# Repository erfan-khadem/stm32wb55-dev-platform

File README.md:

# stm32wb55-dev-platform
An Evaluation and Development Platform For STM32WB55CGU6 MicroController with a few Sensors.

Note that the PCB is designed in 4 layers.

[Schematics pdf](https://github.com/erfan-khadem/stm32wb55-dev-platform/blob/main/stm32wb55-dev.pdf)

[Assembled PCB Picture](https://github.com/erfan-khadem/stm32wb55-dev-platform/blob/main/assembled.jpg?raw=true)

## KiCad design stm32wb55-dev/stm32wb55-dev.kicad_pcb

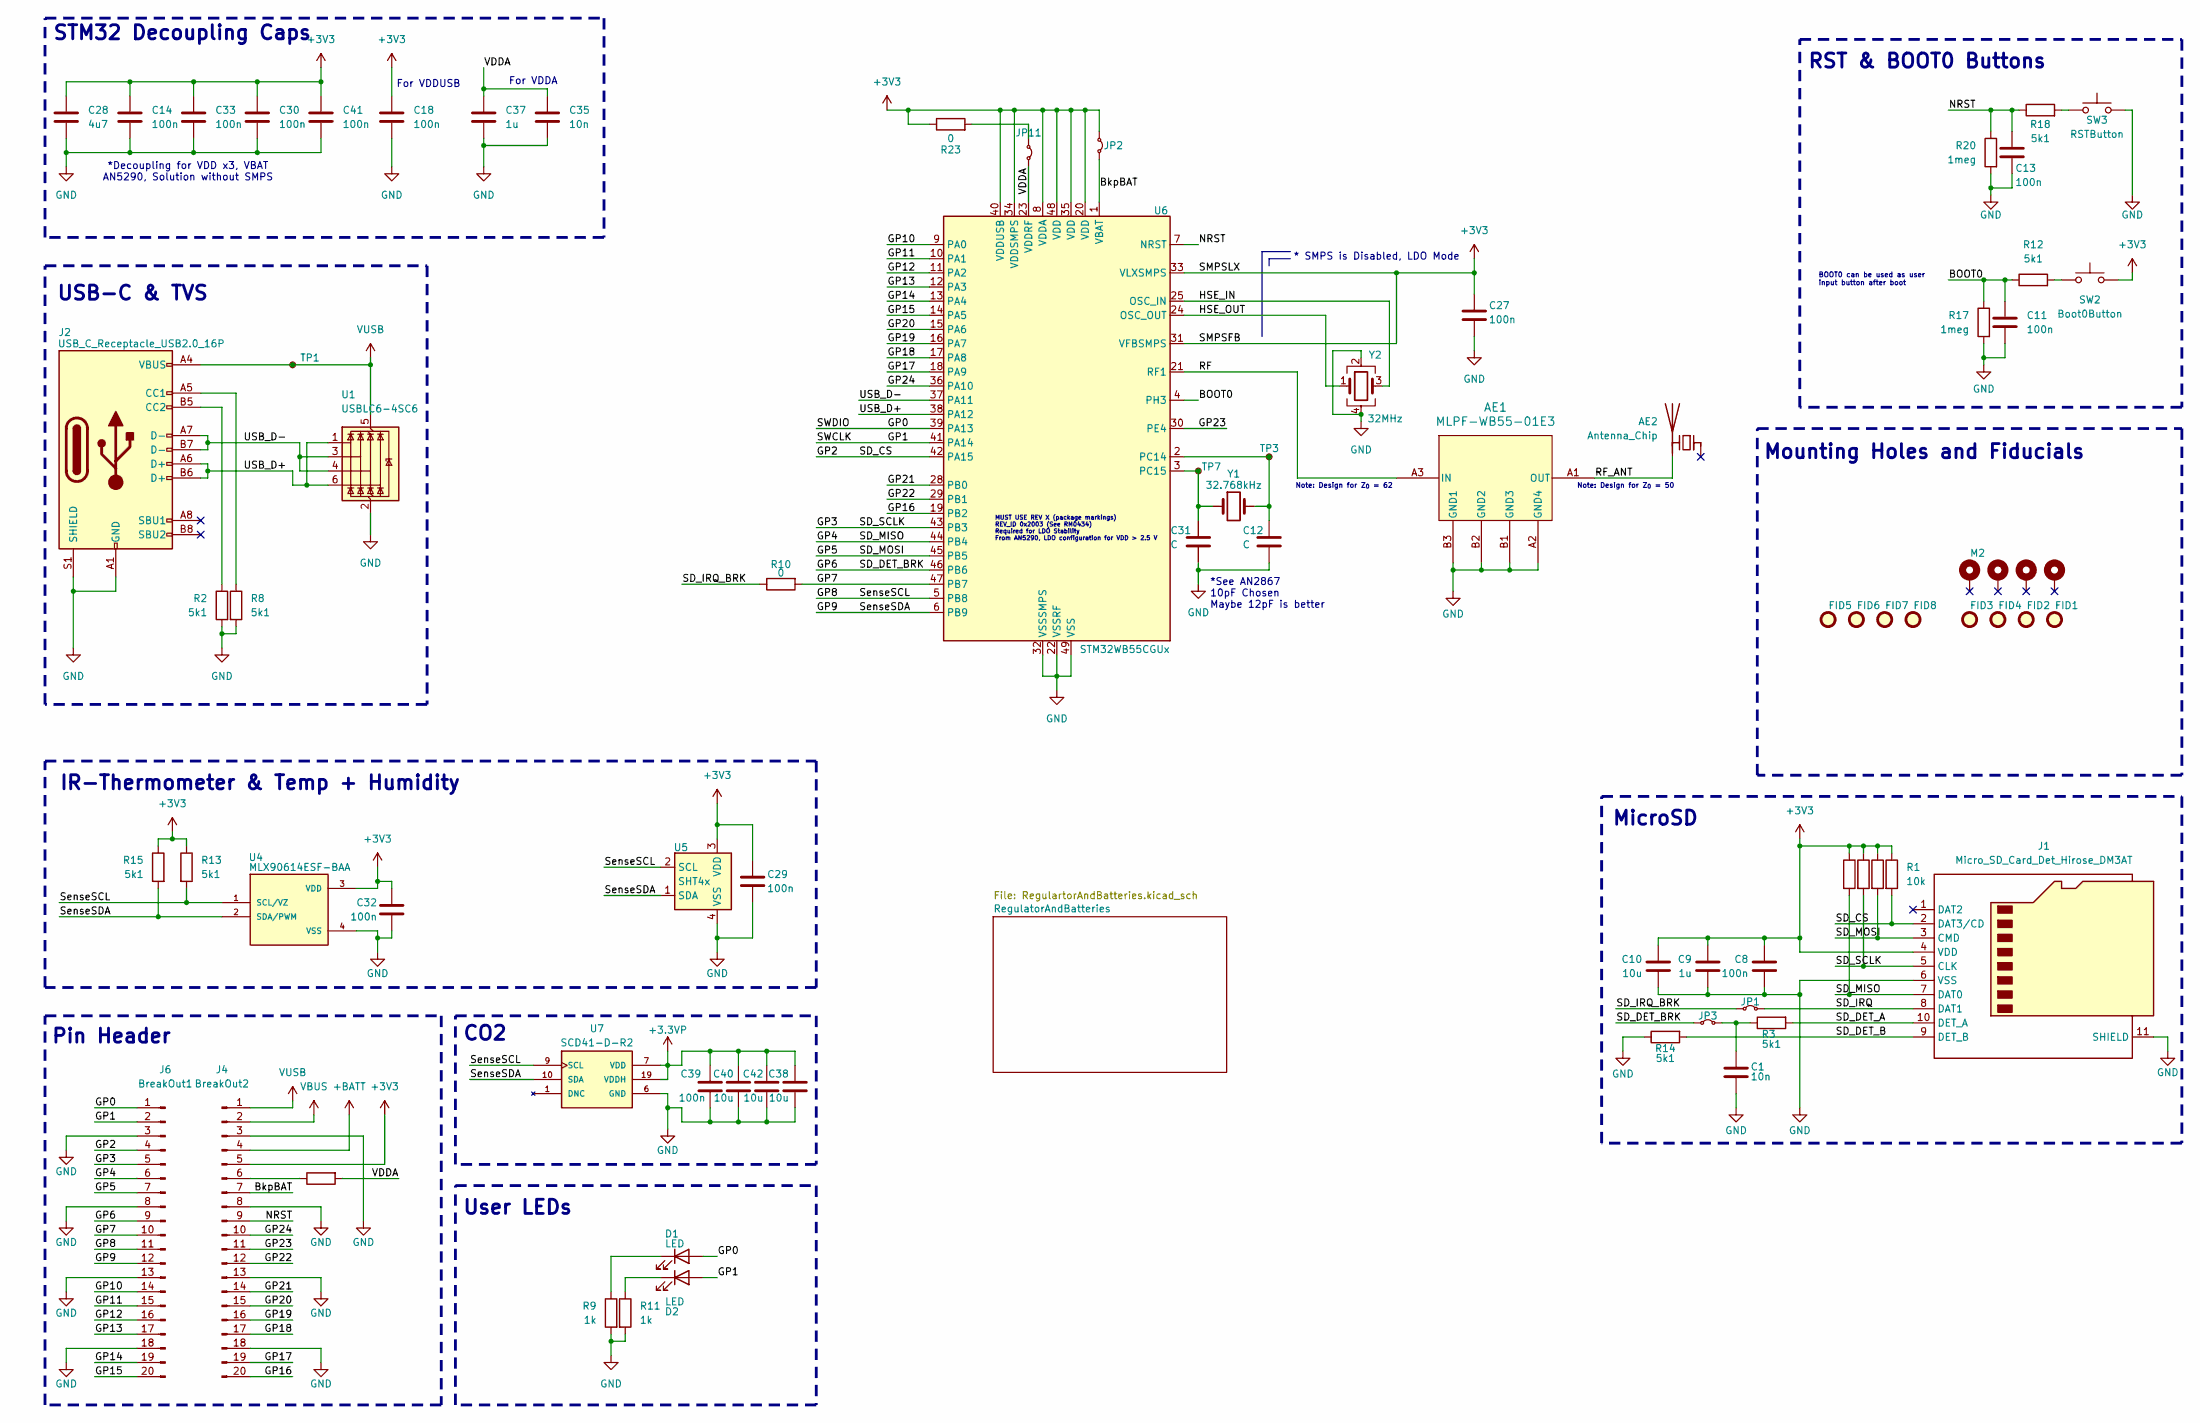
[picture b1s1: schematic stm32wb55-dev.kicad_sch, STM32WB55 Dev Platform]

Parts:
AE1: MLPF-WB55-01E3; MLPF-WB55-01E3_STM-M
AE2: Antenna_Chip; L_1206_3216Metric_Pad1.22x1.90mm_HandSolder
C1, C35: 10n; C_0603_1608Metric_Pad1.08x0.95mm_HandSolder
C8, C11, C13, C14, C18, C27, C29, C30, C32, C33, C39, C41: 100n; C_0603_1608Metric_Pad1.08x0.95mm_HandSolder
C9, C37: 1u; C_0805_2012Metric_Pad1.18x1.45mm_HandSolder
C10: 10u; C_0603_1608Metric_Pad1.08x0.95mm_HandSolder
C12, C31: C; C_0603_1608Metric_Pad1.08x0.95mm_HandSolder
C28: 4u7; C_0805_2012Metric_Pad1.18x1.45mm_HandSolder
C38, C40, C42: 10u; C_0805_2012Metric_Pad1.18x1.45mm_HandSolder
D1, D2: LED; LED_0805_2012Metric_Pad1.15x1.40mm_HandSolder
FID1, FID2, FID3, FID4, FID5, FID6, FID7, FID8: Fiducial; Fiducial_1.5mm_Mask3mm
H1, H2, H3, H4: M2; MountingHole_2.2mm_M2_ISO7380_Pad_TopBottom
J1: Micro_SD_Card_Det_Hirose_DM3AT; microSD_HC_Hirose_DM3AT-SF-PEJM5
J2: USB_C_Receptacle_USB2.0_16P; USB_C_Receptacle_GCT_USB4105-xx-A_16P_TopMnt_Horizontal
J4: BreakOut2; PinHeader_1x20_P2.54mm_Vertical
J6: BreakOut1; PinHeader_1x20_P2.54mm_Vertical
JP1: SD_IRQ_BREAKER; SolderJumper-2_P1.3mm_Bridged_RoundedPad1.0x1.5mm
JP2: VBATBreaker; SolderJumper-2_P1.3mm_Bridged_RoundedPad1.0x1.5mm
JP3: SD_DET_BREAKER; SolderJumper-2_P1.3mm_Bridged_RoundedPad1.0x1.5mm
JP11: VDDABreaker; SolderJumper-2_P1.3mm_Bridged_RoundedPad1.0x1.5mm
R1, R16, R19, R21: 10k; R_0603_1608Metric_Pad0.98x0.95mm_HandSolder
R2, R3, R8, R12, R13, R14, R15, R18: 5k1; R_0603_1608Metric_Pad0.98x0.95mm_HandSolder
R9, R11: 1k; R_0603_1608Metric_Pad0.98x0.95mm_HandSolder
R10, R22, R23: 0; R_1206_3216Metric_Pad1.30x1.75mm_HandSolder
R17, R20: 1meg; R_0603_1608Metric_Pad0.98x0.95mm_HandSolder
SW2: Boot0Button; SW_Push_1P1T_NO_Vertical_Wuerth_434133025816
SW3: RSTButton; SW_Push_1P1T_NO_Vertical_Wuerth_434133025816
TP1: USBPowerConnMonitor; TestPoint_Pad_D1.5mm
TP3: LSEMon2; TestPoint_Pad_D1.0mm
TP7: LSEMon1; TestPoint_Pad_D1.0mm
U1: USBLC6-4SC6; SOT-23-6
U4: MLX90614ESF-BAA; TO254P942H425-4; PARTREV 13
U5: SHT4x; Sensirion_DFN-4_1.5x1.5mm_P0.8mm_SHT4x_NoCentralPad
U6: STM32WB55CGUx; QFN-48-1EP_7x7mm_P0.5mm_EP5.6x5.6mm
U7: SCD41-D-R2; XDCR_SCD41-D-R2; PARTREV 1.2; DigiKey_Part_Number 1649-SCD41-D-R2CT-ND
Y1: 32.768kHz; Crystal_SMD_3215-2Pin_3.2x1.5mm
Y2: 32MHz; Crystal_SMD_2016-4Pin_2.0x1.6mm

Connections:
+3.3VP: C38.1, C39.1, C40.1, C42.1, U7.7 (VDD), U7.19 (VDDH); also elsewhere on the board
+3V3: C8.1, C9.1, C10.1, C14.1, C18.1, C27.1, C28.1, C29.1, C30.1, C32.1, C33.1, C41.1, J1.4 (VDD), J4.5, JP2.1 (A), R1.1, R13.1, R15.1, R16.1, R19.1, R21.1, R23.1, SW2.2, U4.3 (VDD), U5.3 (VDD), U6.8 (VDDA), U6.20 (VDD), U6.31 (VFBSMPS), U6.33 (VLXSMPS), U6.34 (VDDSMPS), U6.35 (VDD), U6.40 (VDDUSB), U6.48 (VDD); also elsewhere on the board
+BATT: J4.4; also elsewhere on the board
/BOOT0: C11.1, R12.1, R17.1, U6.4 (PH3)
/BkpBAT: J4.7, JP2.2 (B), U6.1 (VBAT)
/GP0: D1.2 (A), J6.1, U6.39 (PA13)
/GP1: D2.2 (A), J6.2, U6.41 (PA14)
/GP2: J1.2 (DAT3/CD), J6.4, R1.2, U6.42 (PA15)
/GP3: J1.5 (CLK), J6.5, R19.2, U6.43 (PB3)
/GP4: J1.7 (DAT0), J6.6, R21.2, U6.44 (PB4)
/GP5: J1.3 (CMD), J6.7, R16.2, U6.45 (PB5)
/GP6: J6.9, JP3.1 (A), U6.46 (PB6)
/GP7: J6.10, R10.2, U6.47 (PB7)
/GP8: J6.11, R13.2, U4.1 (SCL/VZ), U5.2 (SCL), U6.5 (PB8), U7.9 (SCL)
/GP9: J6.12, R15.2, U4.2 (SDA/PWM), U5.1 (SDA), U6.6 (PB9), U7.10 (SDA)
/GP10: J6.14, U6.9 (PA0)
/GP11: J6.15, U6.10 (PA1)
/GP12: J6.16, U6.11 (PA2)
/GP13: J6.17, U6.12 (PA3)
/GP14: J6.19, U6.13 (PA4)
/GP15: J6.20, U6.14 (PA5)
/GP16: J4.20, U6.19 (PB2)
/GP17: J4.19, U6.18 (PA9)
/GP18: J4.17, U6.17 (PA8)
/GP19: J4.16, U6.16 (PA7)
/GP20: J4.15, U6.15 (PA6)
/GP21: J4.14, U6.28 (PB0)
/GP22: J4.12, U6.29 (PB1)
/GP23: J4.11, U6.30 (PE4)
/GP24: J4.10, U6.36 (PA10)
/HSE_IN: U6.25 (OSC_IN), Y2.3
/HSE_OUT: U6.24 (OSC_OUT), Y2.1
/NRST: C13.1, J4.9, R18.1, R20.1, U6.7 (NRST)
/RF: AE1.A3 (IN), U6.21 (RF1)
/RF_ANT: AE1.A1 (OUT), AE2.2 (PCB_Trace)
/SD_DET_A: J1.10 (DET_A), R3.2
/SD_DET_B: J1.9 (DET_B), R14.2
/SD_IRQ: J1.8 (DAT1), JP1.2 (B)
/SD_IRQ_BRK: JP1.1 (A), R10.1
/USB_D+: J2.A6 (D+), J2.B6 (D+), U1.1 (I/O1), U1.6 (I/O4), U6.38 (PA12)
/USB_D-: J2.A7 (D-), J2.B7 (D-), U1.3 (I/O2), U1.4 (I/O3), U6.37 (PA11)
/VDDA: C35.1, C37.1, JP11.2 (B), R22.2, U6.23 (VDDRF)
GND: AE1.A2 (GND4), AE1.B1 (GND3), AE1.B2 (GND2), AE1.B3 (GND1), C1.2, C8.2, C9.2, C10.2, C11.2, C12.2, C13.2, C14.2, C18.2, C27.2, C28.2, C29.2, C30.2, C31.2, C32.2, C33.2, C35.2, C37.2, C38.2, C39.2, C40.2, C41.2, C42.2, J1.6 (VSS), J1.11 (SHIELD), J2.A1 (GND), J2.A12 (GND), J2.B1 (GND), J2.B12 (GND), J2.S1 (SHIELD), J4.3, J4.8, J4.13, J4.18, J6.3, J6.8, J6.13, J6.18, R2.2, R8.2, R9.2, R11.2, R14.1, R17.2, R20.2, SW3.2, U1.2 (GND), U4.4 (VSS), U5.4 (VSS), U6.22 (VSSRF), U6.32 (VSSSMPS), U6.49 (VSS), U7.6 (GND), U7.20 (GND), U7.21 (GND), Y2.2, Y2.4; also elsewhere on the board
unnamed: D1.1 (K), R9.1
unnamed: D2.1 (K), R11.1
unnamed: J2.A5 (CC1), R8.1
unnamed: J2.B5 (CC2), R2.1
unnamed: J4.6, R22.1
unnamed: C1.1, JP3.2 (B), R3.1
unnamed: JP11.1 (A), R23.2
unnamed: R12.2, SW2.1
unnamed: R18.2, SW3.1
unnamed: C12.1, TP3.1, U6.2 (PC14), Y1.2
unnamed: C31.1, TP7.1, U6.3 (PC15), Y1.1
VBUS: J4.2; also elsewhere on the board
VUSB: J2.A4 (VBUS), J2.A9 (VBUS), J2.B4 (VBUS), J2.B9 (VBUS), J4.1, TP1.1, U1.5 (VBUS); also elsewhere on the board

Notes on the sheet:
Note: Design for Z_{0} = 50
Pin Header
Mounting Holes and Fiducials
Note: Design for Z_{0} = 62
*Decoupling for VDD x3, VBAT AN5290, Solution without SMPS
BOOT0 can be used as user input button after boot
RST & BOOT0 Buttons
USB-C & TVS
For VDDA
IR-Thermometer & Temp + Humidity
User LEDs
* SMPS is Disabled, LDO Mode
MicroSD
CO2
*See AN2867 10pF Chosen Maybe 12pF is better
MUST USE REV X (package markings) REV_ID 0x2003 (See RM0434) Required for LDO Stability From AN5290, LDO configuration for VDD > 2.5 V
STM32 Decoupling Caps
For VDDUSB

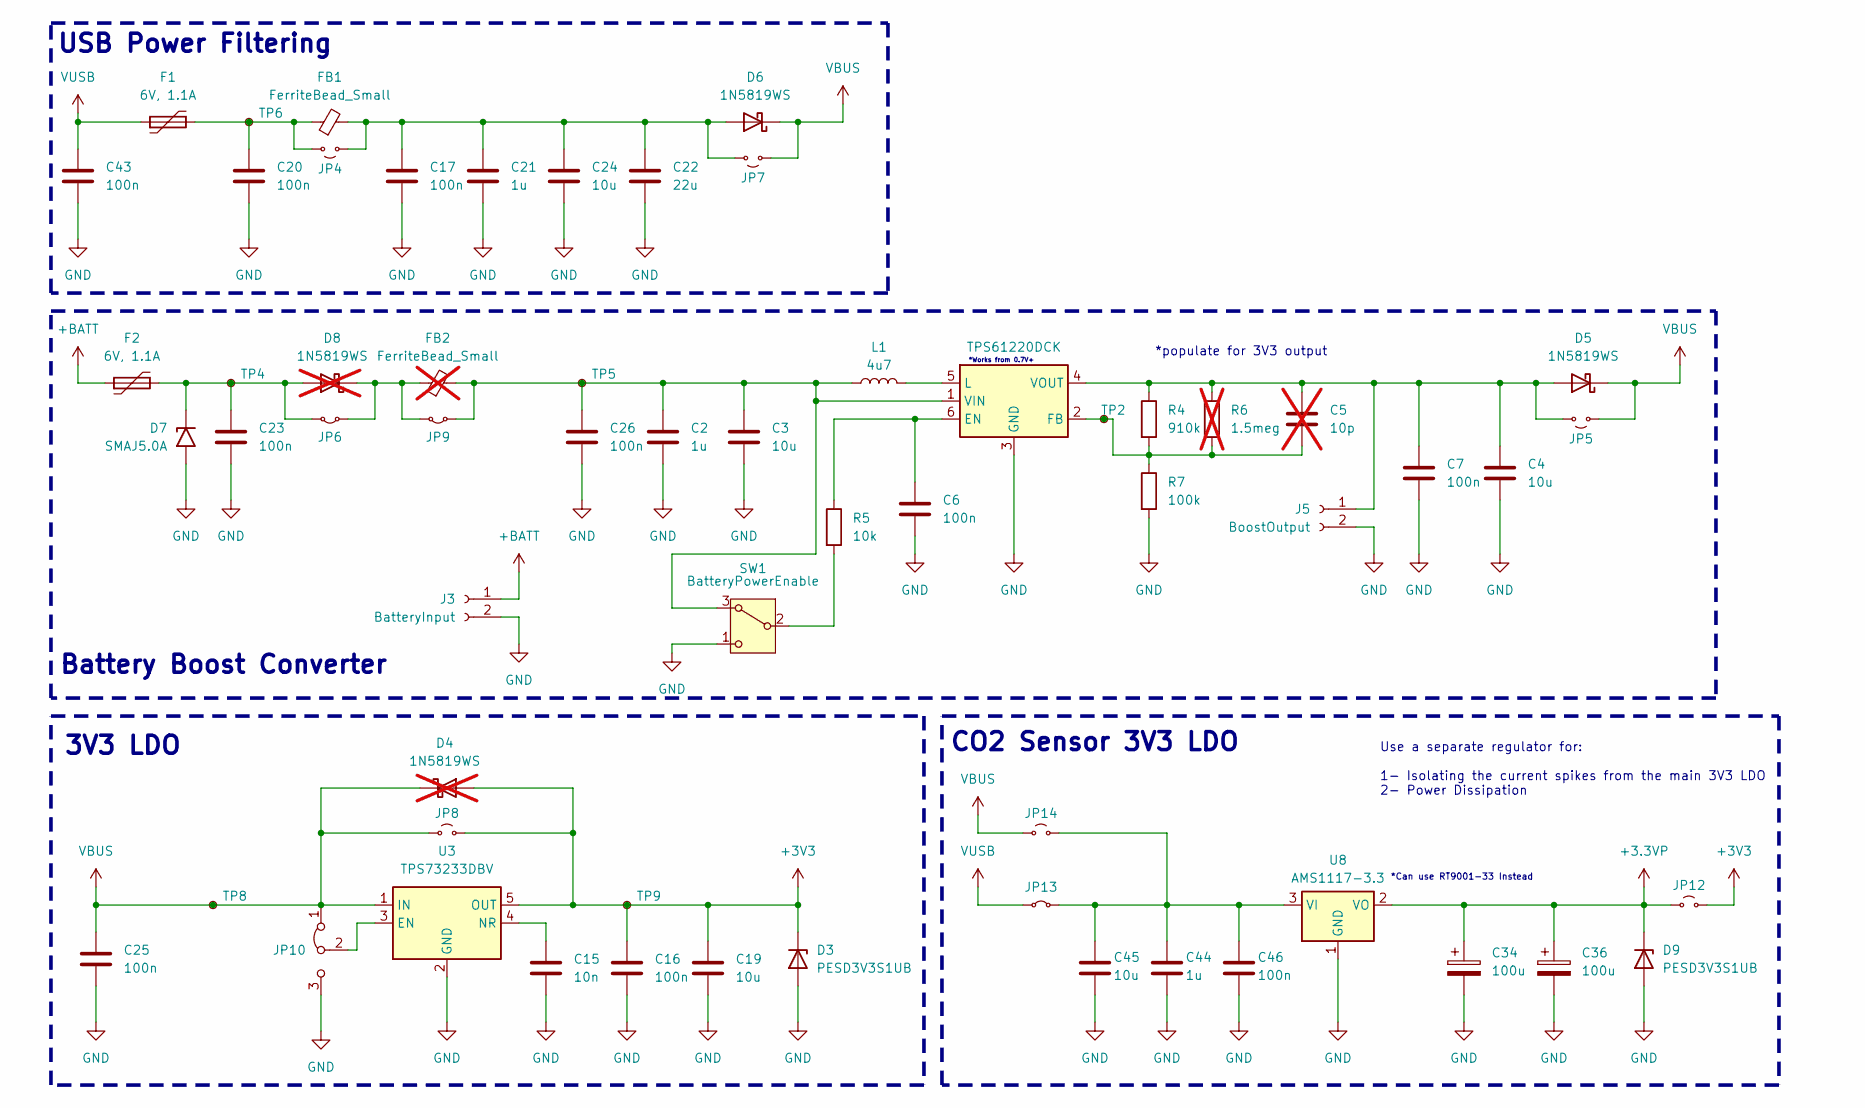
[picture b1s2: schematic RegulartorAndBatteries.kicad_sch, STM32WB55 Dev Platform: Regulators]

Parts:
C2, C21: 1u; C_0805_2012Metric_Pad1.18x1.45mm_HandSolder
C3, C4, C19, C24, C45: 10u; C_0805_2012Metric_Pad1.18x1.45mm_HandSolder
C5: 10p; C_0603_1608Metric_Pad1.08x0.95mm_HandSolder; not fitted
C6, C7, C16, C17, C20, C23, C25, C26, C43, C46: 100n; C_0603_1608Metric_Pad1.08x0.95mm_HandSolder
C15: 10n; C_0603_1608Metric_Pad1.08x0.95mm_HandSolder
C22: 22u; C_0805_2012Metric_Pad1.18x1.45mm_HandSolder
C34, C36: 100u; CP_EIA-3528-21_Kemet-B_HandSolder
C44: 1u; C_0603_1608Metric_Pad1.08x0.95mm_HandSolder
D3, D9: PESD3V3S1UB; D_SOD-523
D4, D8: 1N5819WS; D_SOD-323_HandSoldering; not fitted
D5, D6: 1N5819WS; D_SOD-323_HandSoldering
D7: SMAJ5.0A; D_SMA
F1, F2: 6V, 1.1A; Fuse_1210_3225Metric_Pad1.42x2.65mm_HandSolder
FB1: FerriteBead_Small; L_0805_2012Metric_Pad1.05x1.20mm_HandSolder
FB2: FerriteBead_Small; L_0805_2012Metric_Pad1.05x1.20mm_HandSolder; not fitted
J3: BatteryInput; PinHeader_1x02_P2.54mm_Vertical
J5: BoostOutput; PinHeader_1x02_P2.54mm_Vertical
JP4: BypassVUSBFerriteBead; SolderJumper-2_P1.3mm_Open_TrianglePad1.0x1.5mm
JP5, JP12, JP14: BypassBoostDiode; SolderJumper-2_P1.3mm_Open_TrianglePad1.0x1.5mm
JP6, JP13: BatteryDiodeBypass; SolderJumper-2_P1.3mm_Bridged_RoundedPad1.0x1.5mm
JP7: BypassVUSBDiode; SolderJumper-2_P1.3mm_Open_TrianglePad1.0x1.5mm
JP8: BypassLDO; SolderJumper-2_P1.3mm_Open_TrianglePad1.0x1.5mm
JP9: BypassBatteryFerriteBead; SolderJumper-2_P1.3mm_Bridged_RoundedPad1.0x1.5mm
JP10: LDODisable; SolderJumper-3_P1.3mm_Bridged12_RoundedPad1.0x1.5mm
L1: 4u7; L_1210_3225Metric_Pad1.42x2.65mm_HandSolder
R4: 910k; R_0603_1608Metric_Pad0.98x0.95mm_HandSolder
R5: 10k; R_0603_1608Metric_Pad0.98x0.95mm_HandSolder
R6: 1.5meg; R_0603_1608Metric_Pad0.98x0.95mm_HandSolder; not fitted
R7: 100k; R_0603_1608Metric_Pad0.98x0.95mm_HandSolder
SW1: BatteryPowerEnable; SW_SPDT_PCM12
TP2: BoostFBMon; TestPoint_Pad_D1.0mm
TP4: BattInAlt; TestPoint_Pad_D1.0mm
TP5: BoostVinMon; TestPoint_Pad_D1.0mm
TP6: VUSBProtMon; TestPoint_Pad_D1.0mm
TP8: LDOVinMon; PinHeader_1x01_P2.54mm_Vertical
TP9: LDOOutMon; PinHeader_1x01_P2.54mm_Vertical
U2: TPS61220DCK; Texas_R-PDSO-G6
U3: TPS73233DBV; SOT-23-5_HandSoldering
U8: AMS1117-3.3; SOT-223-3_TabPin2

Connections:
+3.3VP: C34.1, C36.1, D9.1 (K), JP12.2 (B), U8.2 (VO); also elsewhere on the board
+3V3: C16.1, C19.1, D3.1 (K), D4.2 (A), JP8.1 (A), JP12.1 (A), TP9.1, U3.5 (OUT); also elsewhere on the board
+BATT: F2.1, J3.1; also elsewhere on the board
GND: C2.2, C3.2, C4.2, C6.2, C7.2, C15.2, C16.2, C17.2, C19.2, C20.2, C21.2, C22.2, C23.2, C24.2, C25.2, C26.2, C34.2, C36.2, C43.2, C44.2, C45.2, C46.2, D3.2 (A), D7.2 (A2), D9.2 (A), J3.2, J5.2, JP10.3 (B), R7.2, SW1.1 (C), U2.3 (GND), U3.2 (GND), U8.1 (GND); also elsewhere on the board
unnamed: C4.1, C5.1, C7.1, D5.2 (A), J5.1, JP5.1 (A), R4.1, R6.1, U2.4 (VOUT)
unnamed: C17.1, C21.1, C22.1, C24.1, D6.2 (A), FB1.2, JP4.2 (B), JP7.1 (A)
unnamed: C23.1, D7.1 (A1), D8.2 (A), F2.2, JP6.1 (A), TP4.1
unnamed: D8.1 (K), FB2.1, JP6.2 (B), JP9.1 (A)
unnamed: C20.1, F1.2, FB1.1, JP4.1 (A), TP6.1
unnamed: C2.1, C3.1, C26.1, FB2.2, JP9.2 (B), L1.1, SW1.3 (A), TP5.1, U2.1 (VIN)
unnamed: JP10.2 (C), U3.3 (EN)
unnamed: C44.1, C45.1, C46.1, JP13.1 (A), JP14.1 (A), U8.3 (VI)
unnamed: R5.2, SW1.2 (B)
unnamed: C6.1, R5.1, U2.6 (EN)
unnamed: C5.2, R4.2, R6.2, R7.1, TP2.1, U2.2 (FB)
unnamed: L1.2, U2.5 (L)
unnamed: C15.1, U3.4 (NR)
VBUS: C25.1, D4.1 (K), D5.1 (K), D6.1 (K), JP5.2 (B), JP7.2 (B), JP8.2 (B), JP10.1 (A), JP14.2 (B), TP8.1, U3.1 (IN); also elsewhere on the board
VUSB: C43.1, F1.1, JP13.2 (B); also elsewhere on the board

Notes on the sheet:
Battery Boost Converter
*populate for 3V3 output
CO2 Sensor 3V3 LDO
3V3 LDO
USB Power Filtering
Use a separate regulator for: 1- Isolating the current spikes from the main 3V3 LDO 2- Power Dissipation
*Works from 0.7V+
*Can use RT9001-33 Instead

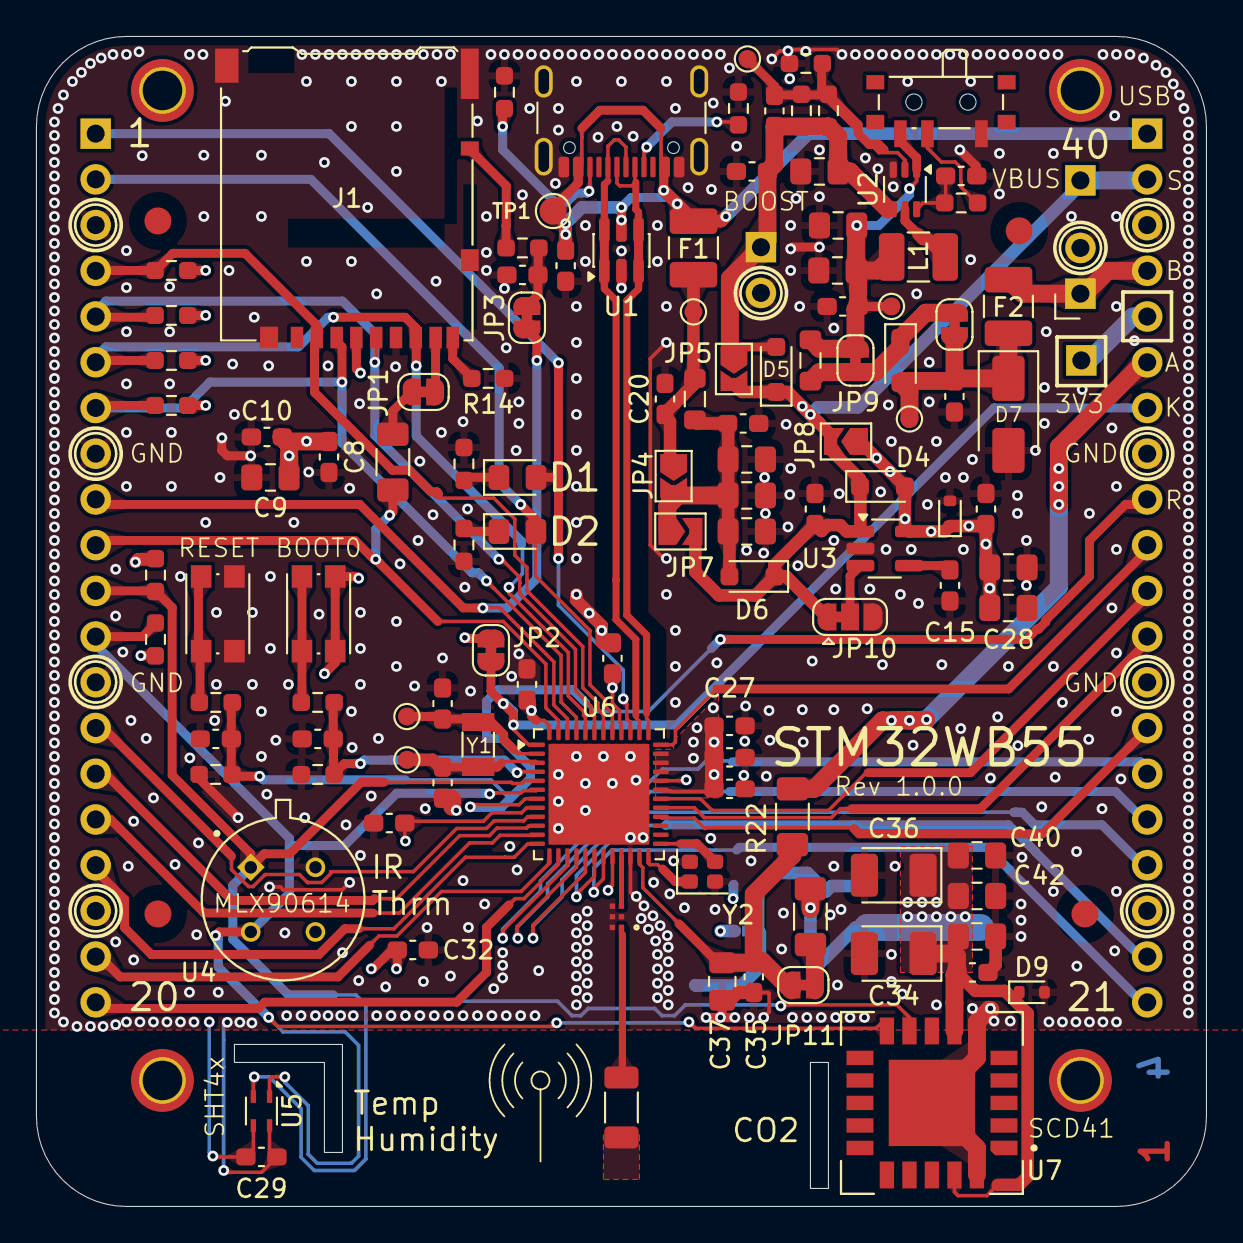
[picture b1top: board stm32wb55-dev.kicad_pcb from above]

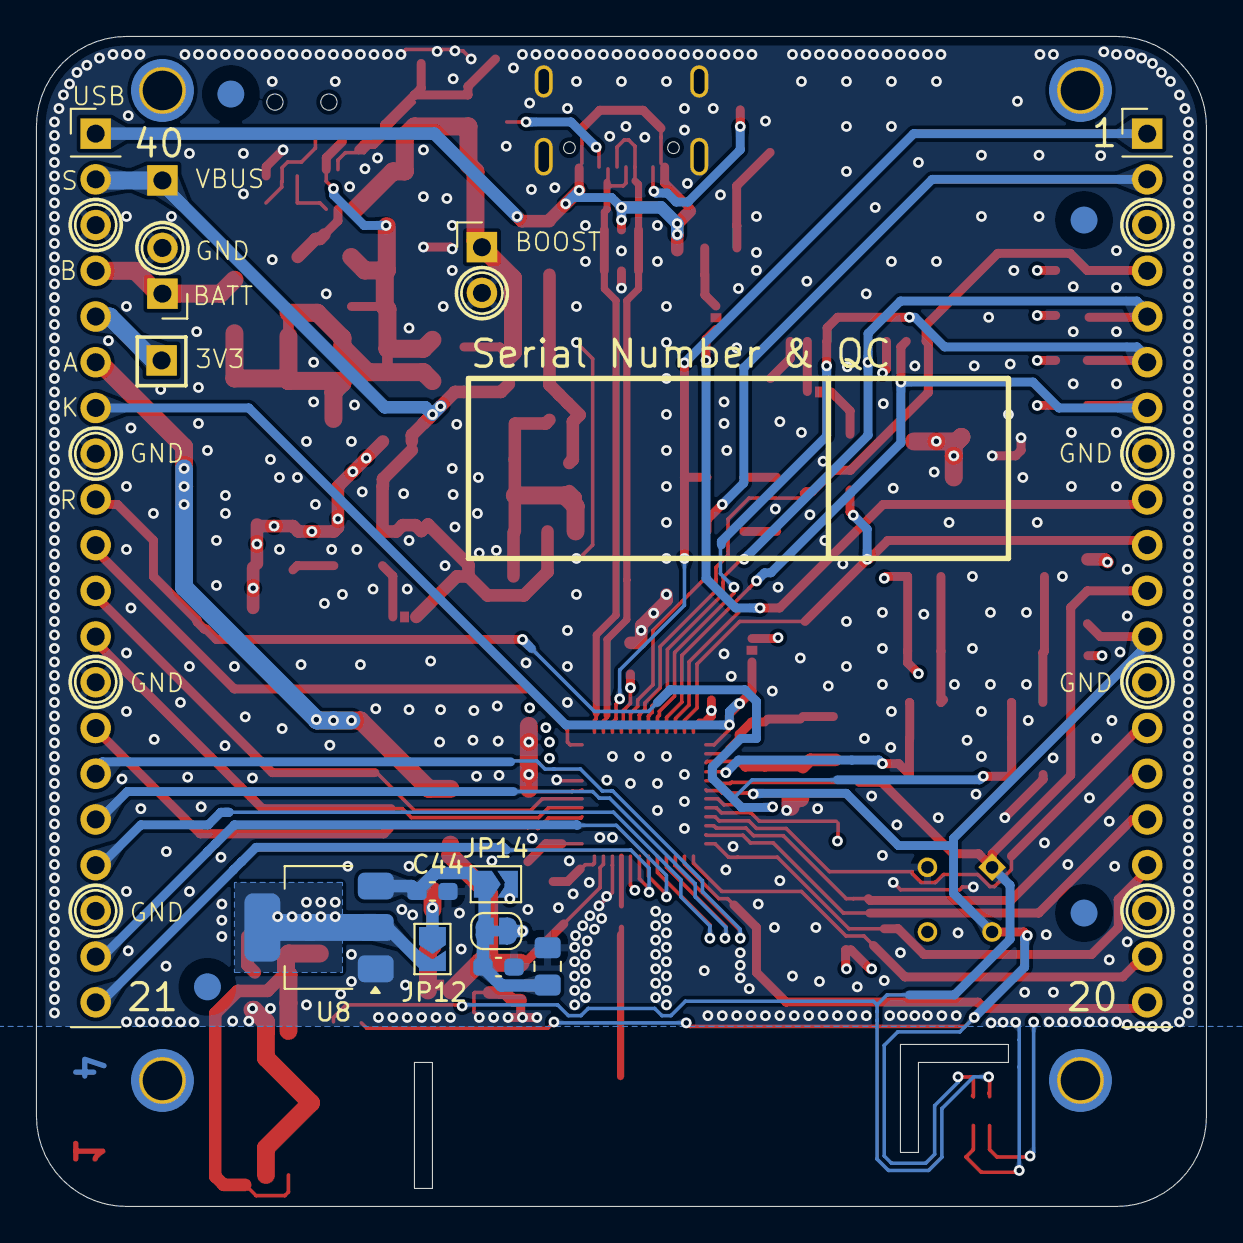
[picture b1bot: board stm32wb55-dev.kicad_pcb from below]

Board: 4 copper layers, 65.0 x 65.0 mm, 139 parts (17 on the bottom side), 69 nets.

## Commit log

2026-02-27 Fix Links
2026-02-27 Improve Readme
